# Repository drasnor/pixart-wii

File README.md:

# pixart-wii
Software and Hardware for working with the Nintendo Wiimote PixArt IR Sensor

Original commits of hardware and software are courtesy of the [Texas A&M University 
Vehicle Systems and Control Laboratory](http://vscl.tamu.edu). See LICENSE for details 
on the open source software and hardware licenses this project uses.

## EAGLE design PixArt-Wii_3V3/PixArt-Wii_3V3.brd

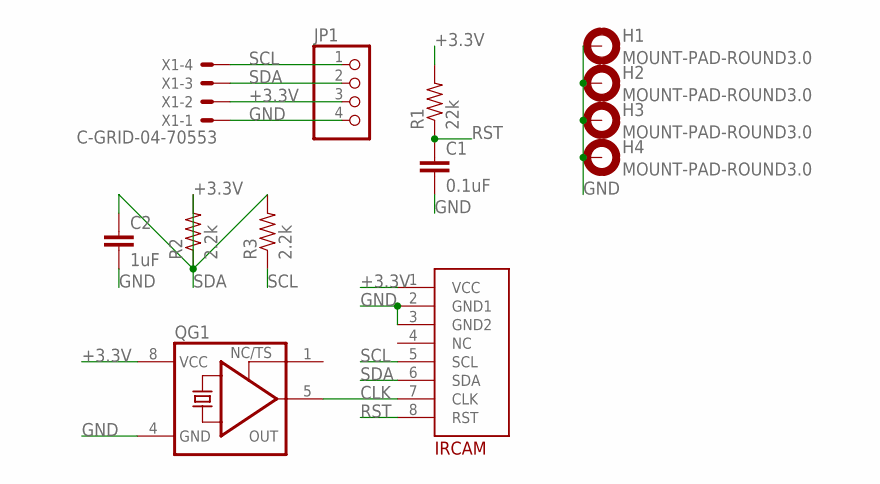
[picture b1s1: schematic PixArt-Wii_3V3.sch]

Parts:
C1: 0.1uF; 1206
C2: 1uF; 1206
H1, H2, H3, H4: MOUNT-PAD-ROUND3.0; 3,0-PAD
IRCAM: PIXART_WII
JP1: PINHD-1X4; 1X04
QG1: XO-8; DIL08S
R1: 22k; 1206
R2, R3: 2.2k; 1206
X1: C-GRID-04-70553; 70553-04

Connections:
+3.3V: C2.1, IRCAM.1 (VCC), JP1.3, QG1.8 (VCC), R1.2, R2.1, R3.2, X1.2
CLK: IRCAM.7 (CLK), QG1.5 (OUT)
GND: C1.2, C2.2, H1.B3,0, H2.B3,0, H3.B3,0, H4.B3,0, IRCAM.2 (GND1), IRCAM.3 (GND2), JP1.4, QG1.4 (GND), X1.1
RST: C1.1, IRCAM.8 (RST), R1.1
SCL: IRCAM.5 (SCL), JP1.1, R3.1, X1.4
SDA: IRCAM.6 (SDA), JP1.2, R2.2, X1.3

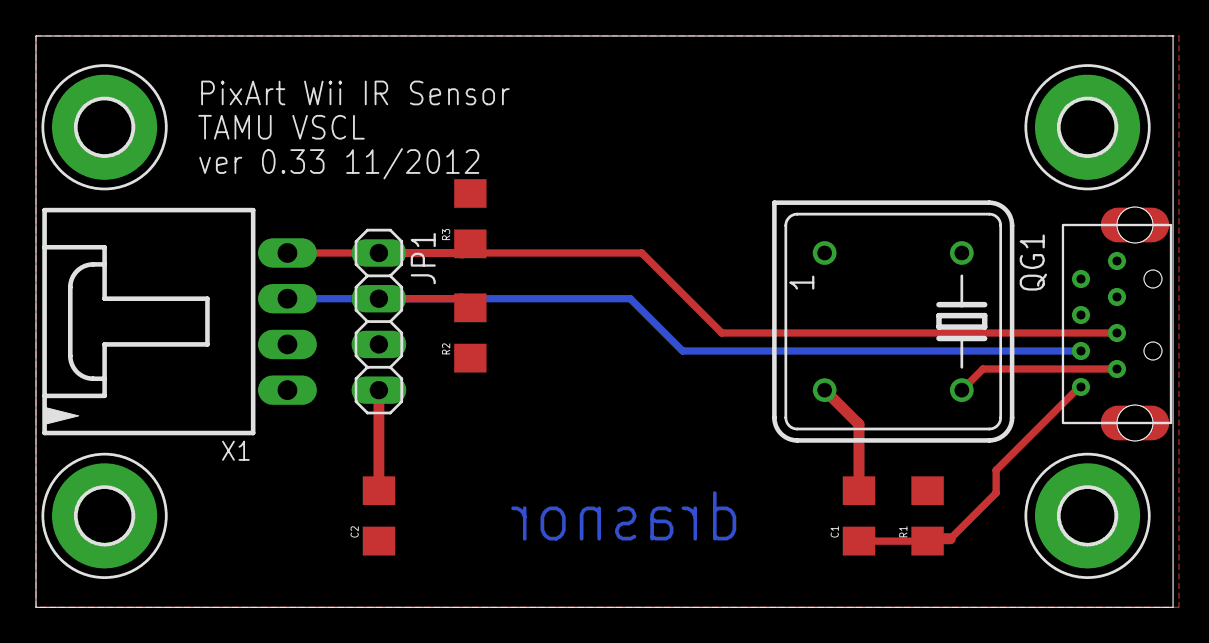
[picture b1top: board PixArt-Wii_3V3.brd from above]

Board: 2 copper layers, 63.2 x 31.7 mm, 13 parts (0 on the bottom side), 6 nets.

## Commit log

2016-01-24 Initial commit of project files, updated LICENSE to include Creative Commons license for hardware, and updated README with basic provenance details.
2016-01-24 Now with actual update to README.

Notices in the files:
parts and their libraries:
SparkFun-Passives: Licensing: CC v3.0 Share-Alike You are welcome to use this library for commercial purposes.
